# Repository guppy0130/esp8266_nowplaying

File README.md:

# ESP8266 Now Playing

Spotify album art on a 64x64 LED matrix

## Materials

* [64x64 LED matrix panel](https://www.adafruit.com/product/5362)
* [controller, networked](https://www.adafruit.com/product/4745)

## Server

The server allows users to auth with Spotify once. It manages token
lifecycle/OAuth2, selecting the correct image and processing it for client
consumption, etc.

```sh
python3.11 -m venv .venv --prompt=.
source ./.venv/bin/activate
pip install -e .
hypercorn server:app --bind 0.0.0.0:3000 --reload --access-logfile - --log-file -
```

You should auth with `/authorize/<your spotify username>` first before letting
the client hit `/user/<your spotify username>`.

Refer to `/docs` for the API docs.

```sh
docker build . -t esp8266-nowplaying:$(python -m setuptools_scm --strip-dev)
```

## Client

Currently connects to `/user/<user>/art` for just the album art. Attach another
display for the track/artists.

You should supply the following in your `settings.toml`:

```env
CIRCUITPY_WIFI_SSID
CIRCUITPY_WIFI_PASSWORD
SERVER_URL
SPOTIFY_USERNAME
```

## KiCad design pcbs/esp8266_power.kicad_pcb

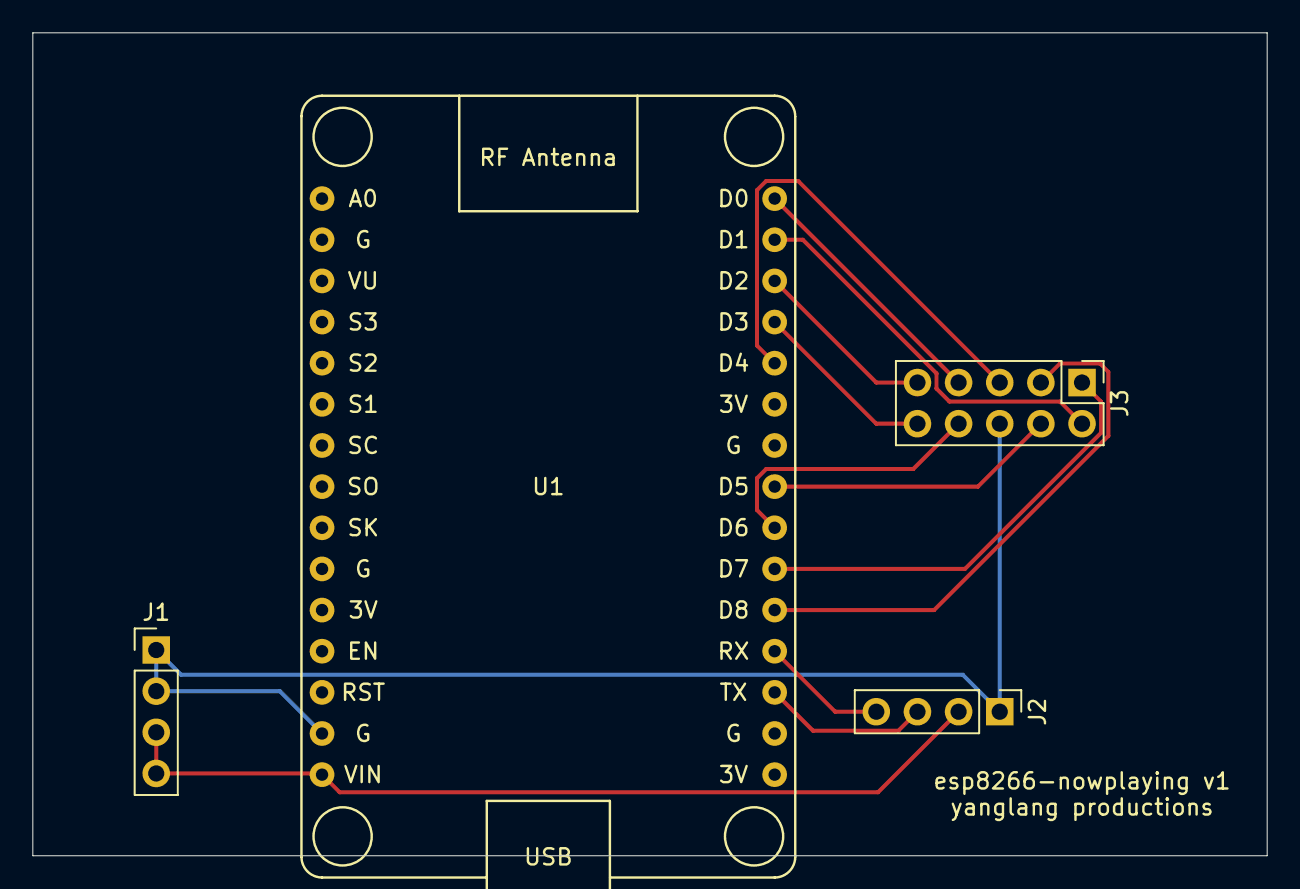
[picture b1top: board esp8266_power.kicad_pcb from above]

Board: 2 copper layers, 76.2 x 50.8 mm, 4 parts (0 on the bottom side), 13 nets.

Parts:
J1: Power; PinHeader_1x04_P2.54mm_Vertical
J2: LCD Module w/ Backpack; PinHeader_1x04_P2.54mm_Vertical
J3: LED Matrix; PinHeader_2x05_P2.54mm_Vertical
U1: NodeMCU_1.0_(ESP-12E); NodeMCU1.0(12-E)

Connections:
+5V: J1.3, J1.4, J2.2, U1.15
/A: J3.2, U1.29
/B: J3.9, U1.28
/C: J3.3, U1.20
/CLK: J3.4, U1.23
/D: J3.8, U1.22
/E: J3.10, U1.27
/LAT: J3.7, U1.30
/OE: J3.5, U1.26
/R1: J3.1, U1.21
/SCL: J2.4, U1.19
/SDA: J2.3, U1.18
GND: J1.1, J1.2, J2.1, J3.6, U1.14

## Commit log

2020-11-30 clear bottom row before writing, fix indexing
2020-11-30 quieter startup, helpful lcd errors
2021-04-05 [3d-prints, pcbs] add some hardware stuff
    * update README to document additions
    * update gitignore to filter new additions
2021-04-13 [server] misc fixups, initial dockerfile
2024-03-10 simplify, v2
2024-03-10 containerize server
2024-03-10 fixup debug from previous commit
2024-03-11 client rtc/ntp updates
    * set rtc to utc; get utc via ntp
